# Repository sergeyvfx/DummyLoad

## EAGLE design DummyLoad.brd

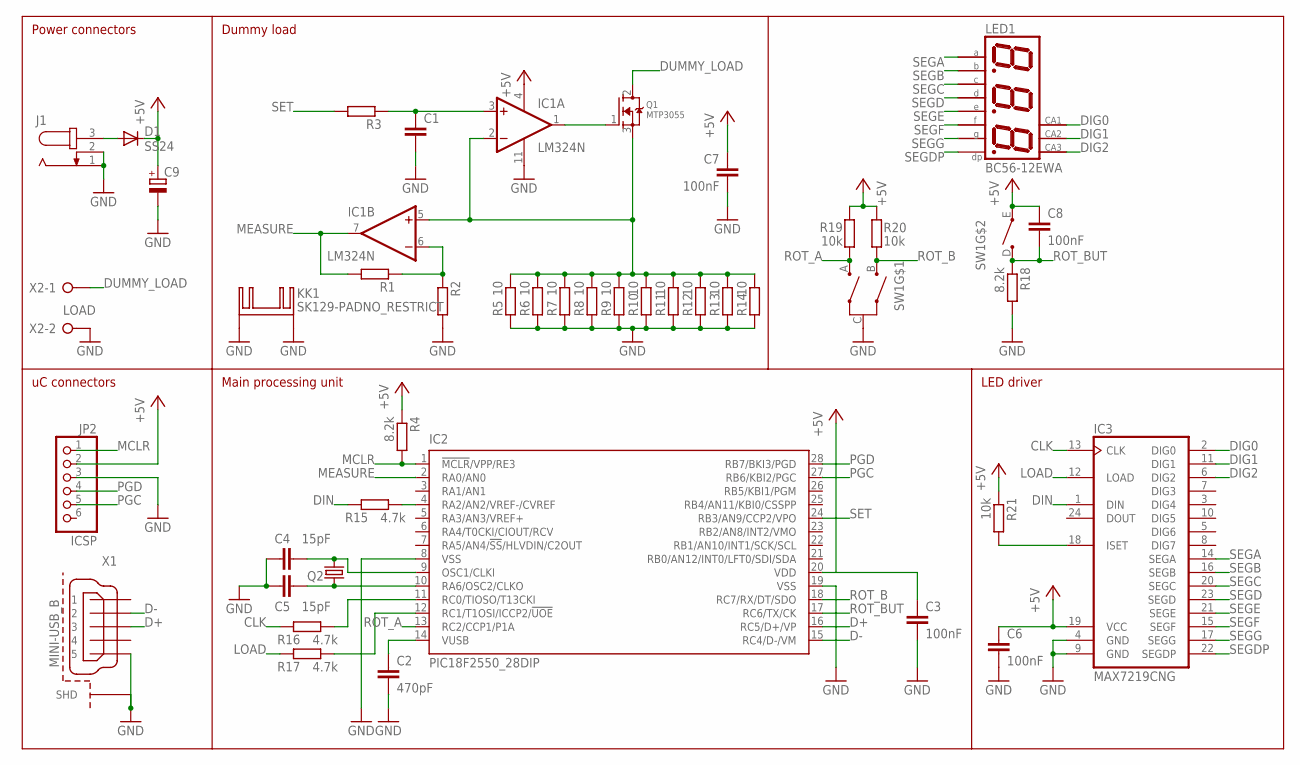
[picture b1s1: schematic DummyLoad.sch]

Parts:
C1: C-EUC1206; C1206
C2: 470pF; C1206
C3, C6, C7, C8: 100nF; C1206
C4, C5: 15pF; C1206
C9: CPOL-EUD/7343-31R; D/7343-31R
D1: SS24; DO214AA
IC1: LM324N; DIL14
IC2: PIC18F2550_28DIP; DIL28-3
IC3: MAX7219CNG; DIL24-3
J1: JACK-PLUG0; SPC4077
JP2: ICSP; 1X06/90
KK1: SK129-PADNO_RESTRICT; SK129-NO_RESTRICT
LED1: BC56-12EWA; BX56-12
Q1: MTP3055; TO220V
Q2: CRYSTALHC49S; HC49/S
R1, R2, R3: R-EU_R1206; R1206
R4, R18: 8.2k; R1206
R5, R6, R7, R8, R9, R10, R11, R12, R13, R14: 10; 0309/12
R15, R16, R17: 4.7k; R1206
R19, R20, R21: 10k; R1206
SW1: EC11B-V-T; EC11B-V
X1: MINI-USB_B; MINI-USB-B
X2: LOAD; W237-132

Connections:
+5V: C3.1, C6.1, C7.1, C8.1, C9.+, D1.C, IC1.4 (V+), IC2.20 (VDD), IC3.19 (VCC), JP2.2, R4.1, R19.1, R20.1, R21.1, SW1.E
CLK: IC3.13 (CLK), R16.2
D+: IC2.16 (RC5/D+/VP), X1.3
D-: IC2.15 (RC4/D-/VM), X1.2
DIG0: IC3.2 (DIG0), LED1.12 (CA)
DIG1: IC3.11 (DIG1), LED1.9 (CA)
DIG2: IC3.6 (DIG2), LED1.8 (CA)
DIN: IC3.1 (DIN), R15.2
DUMMY_LOAD: Q1.2 (D), X2.1
GND: C1.2, C2.2, C3.2, C4.1, C5.1, C6.2, C7.2, C9.-, IC1.11 (V-), IC2.8 (VSS), IC2.19 (VSS), IC3.4 (GND), IC3.9 (GND), J1.1, J1.2, JP2.3, KK1.A2,5, KK1.B2,5, R2.2, R5.2, R6.2, R7.2, R8.2, R9.2, R10.2, R11.2, R12.2, R13.2, R14.2, R18.2, SW1.C, X1.5, X1.M1 (SHD), X1.M2 (SHD), X1.M3 (SHD), X1.M4 (SHD), X2.2
LOAD: IC3.12 (LOAD), R17.2
MCLR: IC2.1 (!MCLR!/VPP/RE3), JP2.1, R4.2
MEASURE: IC1.7 (OUT), IC2.2 (RA0/AN0), R1.2
unnamed: IC1.1 (OUT), Q1.1 (G)
unnamed: IC1.2 (-IN), IC1.5 (+IN), Q1.3 (S), R5.1, R6.1, R7.1, R8.1, R9.1, R10.1, R11.1, R12.1, R13.1, R14.1
unnamed: C4.2, IC2.9 (OSC1/CLKI), Q2.2
unnamed: IC1.6 (-IN), R1.1, R2.1
unnamed: C2.1, IC2.14 (VUSB)
unnamed: C1.1, IC1.3 (+IN), R3.1
unnamed: C5.2, IC2.10 (RA6/OSC2/CLKO), Q2.1
unnamed: IC2.4 (RA2/AN2/VREF-/CVREF), R15.1
unnamed: IC2.11 (RC0/TIOSO/T13CKI), R16.1
unnamed: IC2.12 (RC1/T1OSI/ICCP2/!UOE), R17.1
unnamed: D1.A, J1.3
unnamed: IC3.18 (ISET), R21.2
PGC: IC2.27 (RB6/KBI2/PGC), JP2.5
PGD: IC2.28 (RB7/BKI3/PGD), JP2.4
ROT_A: IC2.13 (RC2/CCP1/P1A), R19.2, SW1.A
ROT_B: IC2.18 (RC7/RX/DT/SDO), R20.2, SW1.B
ROT_BUT: C8.2, IC2.17 (RC6/TX/CK), R18.1, SW1.D
SEGA: IC3.14 (SEGA), LED1.11 (A)
SEGB: IC3.16 (SEGB), LED1.7 (B)
SEGC: IC3.20 (SEGC), LED1.4 (C)
SEGD: IC3.23 (SEGD), LED1.2 (D)
SEGDP: IC3.22 (SEGDP), LED1.3 (DP)
SEGE: IC3.21 (SEGE), LED1.1 (E)
SEGF: IC3.15 (SEGF), LED1.10 (F)
SEGG: IC3.17 (SEGG), LED1.5 (G)
SET: IC2.24 (RB3/AN9/CCP2/VPO), R3.2

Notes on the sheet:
LED driver
Main processing unit
uC connectors
Power connectors
Dummy load

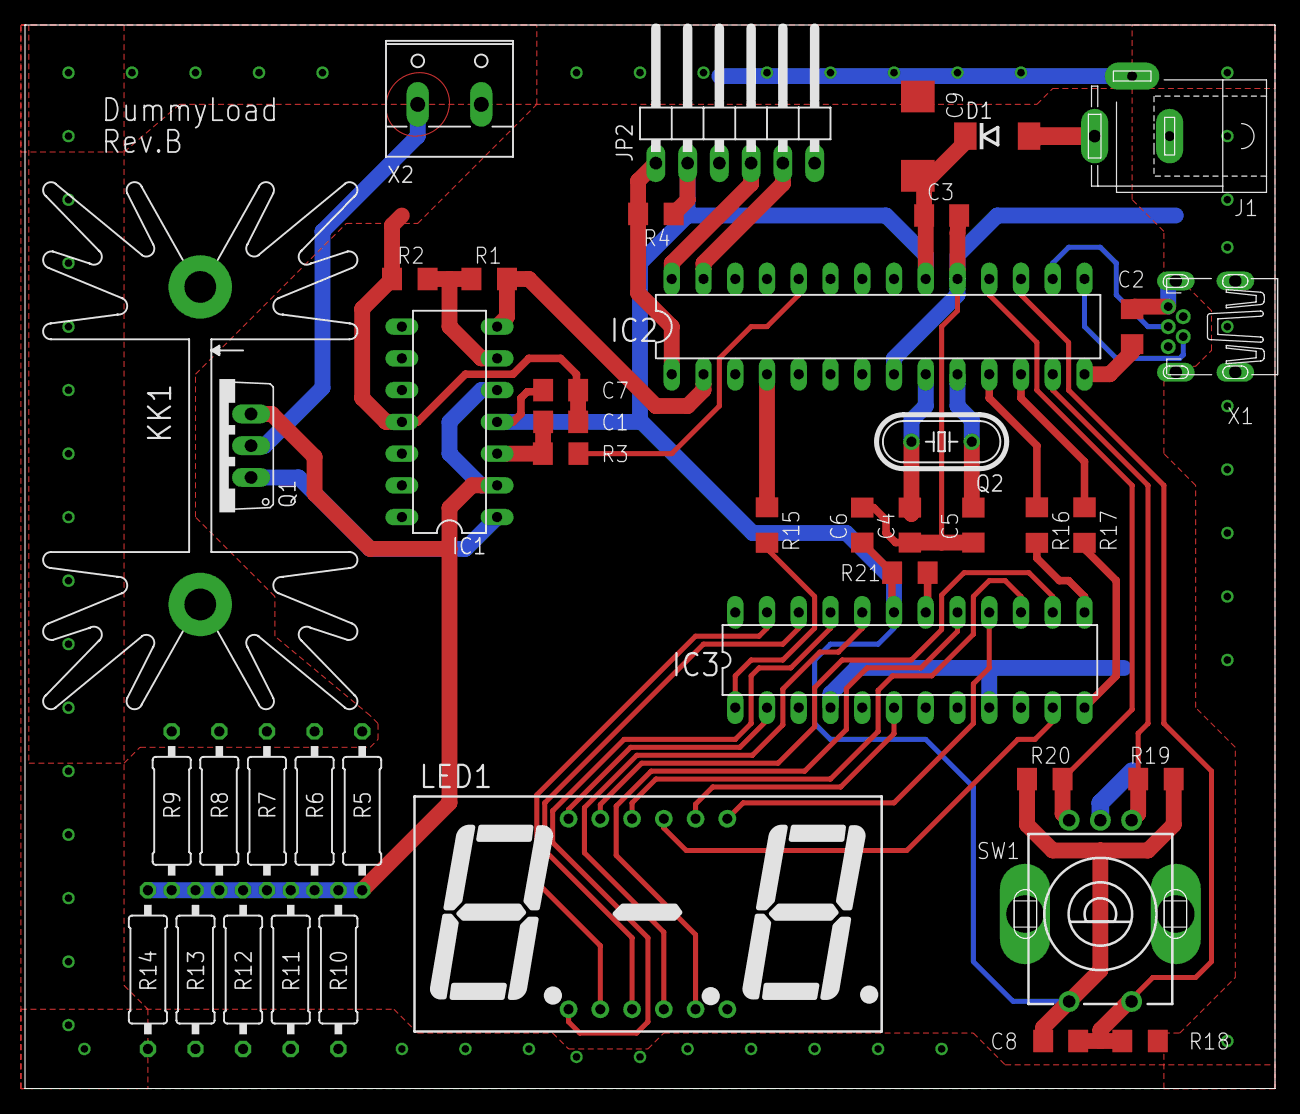
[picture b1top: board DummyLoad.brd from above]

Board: 2 copper layers, 100.0 x 85.1 mm, 43 parts (0 on the bottom side), 39 nets.

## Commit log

2017-01-21 Initial commit of Rev.A with firmware
2017-01-21 Update to latest local version
